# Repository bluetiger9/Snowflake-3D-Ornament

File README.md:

# Snowflake-3D-Ornament

3D Snowflake Ornament with RGB Lights and BLE connectivity

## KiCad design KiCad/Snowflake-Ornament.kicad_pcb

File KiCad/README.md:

# Snowflake 3D Ornament / KiCad files

Uses KiCad 8.x

License: CC BY 4.0

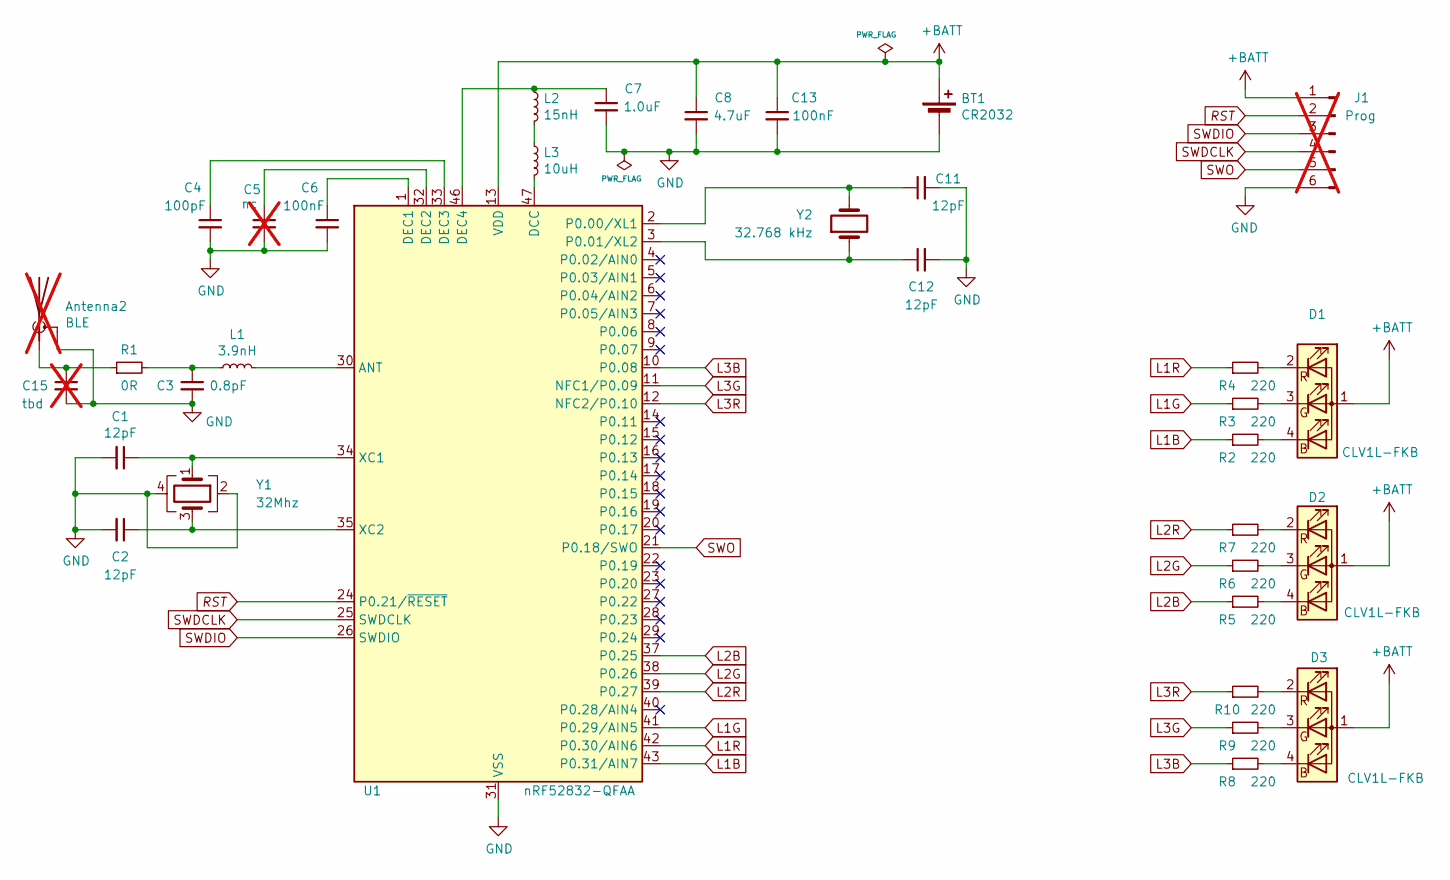
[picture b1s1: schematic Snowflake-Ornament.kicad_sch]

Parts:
Antenna2: BLE; Texas_SWRA117D_2.4GHz_Right; not fitted
BT1: CR2032; BatteryHolder_Keystone_3034_1x20mm
C1, C2, C11, C12: 12pF; C_0603_1608Metric
C3: 0.8pF; C_0603_1608Metric
C4: 100pF; C_0603_1608Metric
C5: nc; C_0603_1608Metric; not fitted
C6, C13: 100nF; C_0603_1608Metric
C7: 1.0uF; C_0603_1608Metric
C8: 4.7uF; C_0603_1608Metric
C15: tbd; C_0603_1608Metric; not fitted
D1, D2, D3: CLV1L-FKB; LED-CREE-CLV1L-FKB
J1: Prog; PinHeader_1x06_P2.00mm_Pad; not fitted
L1: 3.9nH; L_0603_1608Metric
L2: 15nH; L_0603_1608Metric
L3: 10uH; L_0603_1608Metric
R1: 0R; R_0603_1608Metric
R2, R3, R4, R5, R6, R7, R8, R9, R10: 220; R_0603_1608Metric
U1: nRF52832-QFAA; QFN-48-1EP_6x6mm_P0.4mm_EP4.66x4.66mm
Y1: 32Mhz; Crystal_SMD_2016-4Pin_2.0x1.6mm
Y2: 32.768 kHz; Crystal_SMD_3215-2Pin_3.2x1.5mm

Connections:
+BATT: BT1.1 (+), C8.1, C13.1, D1.1 (A), D2.1 (A), D3.1 (A), J1.1, U1.13 (VDD), U1.36 (VDD), U1.48 (VDD)
GND: Antenna2.2 (Shield), BT1.2 (-), C1.2, C2.2, C3.2, C4.2, C5.2, C6.2, C7.2, C8.2, C11.2, C12.2, C13.2, C15.2, J1.6, U1.31 (VSS), U1.45 (VSS), U1.49 (VSS), Y1.2, Y1.4
L1B: R2.1, U1.43 (P0.31/AIN7)
L1G: R3.1, U1.41 (P0.29/AIN5)
L1R: R4.1, U1.42 (P0.30/AIN6)
L2B: R5.1, U1.37 (P0.25)
L2G: R6.1, U1.38 (P0.26)
L2R: R7.1, U1.39 (P0.27)
L3B: R8.1, U1.10 (P0.08)
L3G: R9.1, U1.11 (NFC1/P0.09)
L3R: R10.1, U1.12 (NFC2/P0.10)
unnamed: Antenna2.1 (A), C15.1, R1.1
unnamed: C3.1, L1.1, R1.2
unnamed: D1.4 (BK), R2.2
unnamed: D1.3 (GK), R3.2
unnamed: D1.2 (RK), R4.2
unnamed: D2.4 (BK), R5.2
unnamed: D2.3 (GK), R6.2
unnamed: D2.2 (RK), R7.2
unnamed: D3.4 (BK), R8.2
unnamed: D3.3 (GK), R9.2
unnamed: D3.2 (RK), R10.2
unnamed: L2.2, L3.1
unnamed: L1.2, U1.30 (ANT)
unnamed: L3.2, U1.47 (DCC)
unnamed: C6.1, U1.1 (DEC1)
unnamed: C5.1, U1.32 (DEC2)
unnamed: C4.1, U1.33 (DEC3)
unnamed: C7.1, L2.1, U1.46 (DEC4)
unnamed: C11.1, U1.2 (P0.00/XL1), Y2.2
unnamed: C12.1, U1.3 (P0.01/XL2), Y2.1
unnamed: C1.1, U1.34 (XC1), Y1.1
unnamed: C2.1, U1.35 (XC2), Y1.3
RST: J1.2, U1.24 (P0.21/~RESET)
SWDCLK: J1.4, U1.25 (SWDCLK)
SWDIO: J1.3, U1.26 (SWDIO)
SWO: J1.5, U1.21 (P0.18/SWO)

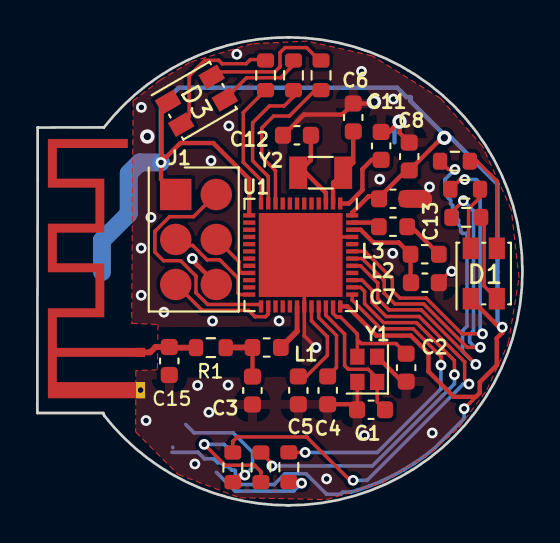
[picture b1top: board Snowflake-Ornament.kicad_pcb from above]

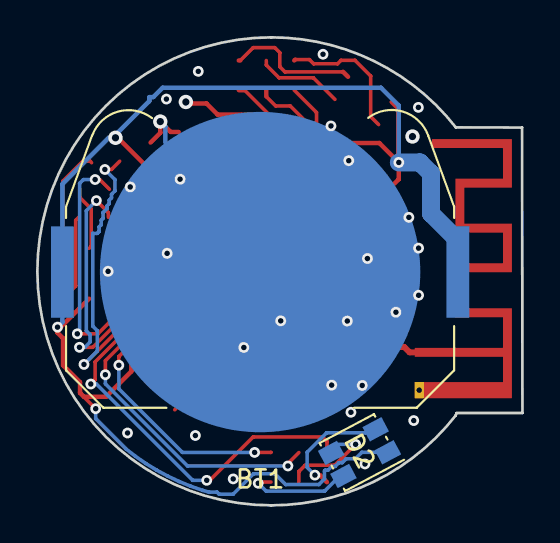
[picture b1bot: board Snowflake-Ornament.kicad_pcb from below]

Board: 4 copper layers, 27.0 x 26.0 mm, 34 parts (2 on the bottom side), 37 nets.

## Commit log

2024-12-21 Added 3D + Electronics + Firmware files
